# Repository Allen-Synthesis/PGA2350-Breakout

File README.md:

# PGA2350-breakout
### Pimoroni PGA2350 Breakout board for breadboard development of Eurorack modules

At the time I'm writing this, the only development board I can find for sale which utilises the B variant of the RP2350 *and* breaks out all of the extra ADCs it offers, is the [Pimoroni PGA2350](https://shop.pimoroni.com/products/pga2350?variant=42092629229651), however it is not a breadboard compatible.  
This board adapts the PGA2350 to allow it to be used for Eurorack development with a breadboard, breaking out all required connections including routing Eurorack power from a standard header to pin headers which can be connected to a breadboard's rails using jumper wire.  
The USB connections are arranged so that an [Adafruit USB Micro-B Breakout Board](https://www.adafruit.com/product/1833) (also sold by [Pimoroni](https://shop.pimoroni.com/products/adafruit-usb-micro-b-breakout-board?variant=821196557)) can be soldered directly to the board.

*NOTE: The first PCB order for these boards was tested on 10/09/2024 and appears to all work as expected. Not every GPIO has been tested, however the design is likely functional. Aesthetic improvements for version 1.1 (outlined below) have now been applied but no new boards have yet been ordered for testing. Order using the files in this repository with my blessing but at your own risk*

Pending changes based on version 1.0:
1. ~~Increment version to 1.1~~
1. ~~Alter pin header footprints to remove square pad for 1x2, 1x5, and 2x5~~
1. ~~Add JLC PCB order number text to the back~~
1. ~~Use consistent . or / in version date~~
1. ~~Remove J12 reference text~~
1. ~~Add ground stitching vias~~
1. ~~Use arrow to label PGA2350 and then use internal space to show orientation~~
1. Measure the USB breakout board and adjust position so that the edge is flush (USB already flush enough)
1. ~~Add lines between the labels and pins for rest of the headers as has been done for the GPIO headers~~
1. Add artwork to the back (and front?) to make use of the space (Text rearranged and logos swapped to copper layer, no more art added)

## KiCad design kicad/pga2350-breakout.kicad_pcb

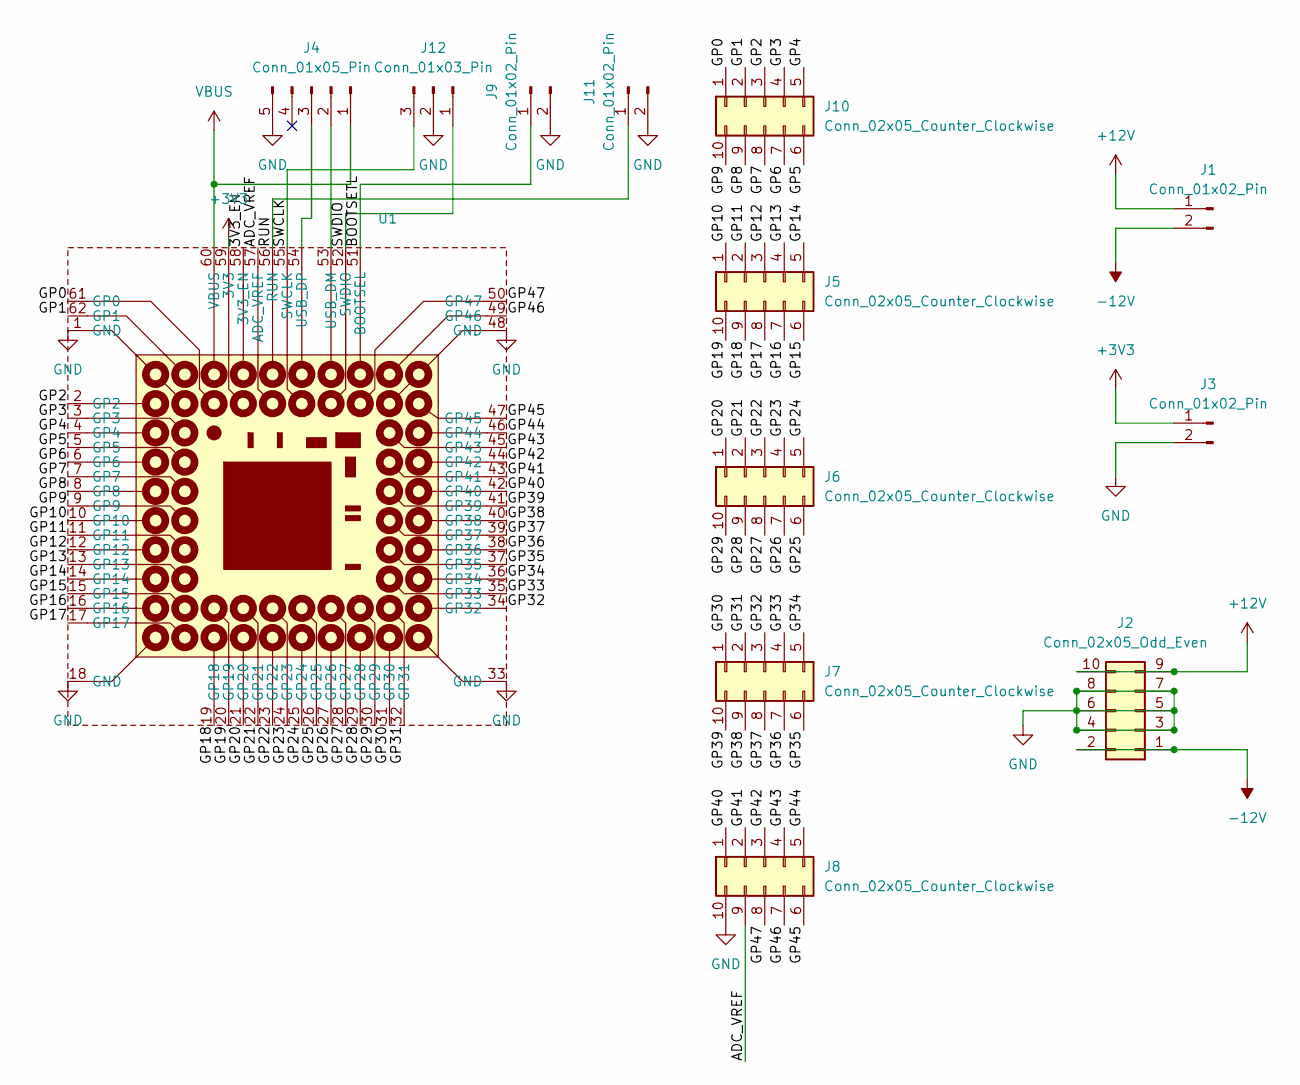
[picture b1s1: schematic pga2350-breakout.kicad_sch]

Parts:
J1, J3, J9, J11: Conn_01x02_Pin; pin-socket-2.54mm-01x02
J2: Conn_02x05_Odd_Even; power-header-10-pin
J4: Conn_01x05_Pin; pin-header-2.54mm-01x05
J5, J6, J7, J8, J10: Conn_02x05_Counter_Clockwise; pin-socket-2.54mm-02x05
J12: Conn_01x03_Pin; pin-header-2.54mm-01x03
U1: PGA2350

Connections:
+3V3: J3.1, U1.59 (3V3)
+12V: J1.1, J2.9, J2.10
-12V: J1.2, J2.1, J2.2
/3V3_EN: U1.58 (3V3_EN)
/ADC_VREF: J8.9, U1.57 (ADC_VREF)
/BOOTSETL: J9.1, U1.51 (BOOTSEL)
/GP0: J10.1, U1.61 (GP0)
/GP1: J10.2, U1.62 (GP1)
/GP2: J10.3, U1.2 (GP2)
/GP3: J10.4, U1.3 (GP3)
/GP4: J10.5, U1.4 (GP4)
/GP5: J10.6, U1.5 (GP5)
/GP6: J10.7, U1.6 (GP6)
/GP7: J10.8, U1.7 (GP7)
/GP8: J10.9, U1.8 (GP8)
/GP9: J10.10, U1.9 (GP9)
/GP10: J5.1, U1.10 (GP10)
/GP11: J5.2, U1.11 (GP11)
/GP12: J5.3, U1.12 (GP12)
/GP13: J5.4, U1.13 (GP13)
/GP14: J5.5, U1.14 (GP14)
/GP15: J5.6, U1.15 (GP15)
/GP16: J5.7, U1.16 (GP16)
/GP17: J5.8, U1.17 (GP17)
/GP18: J5.9, U1.19 (GP18)
/GP19: J5.10, U1.20 (GP19)
/GP20: J6.1, U1.21 (GP20)
/GP21: J6.2, U1.22 (GP21)
/GP22: J6.3, U1.23 (GP22)
/GP23: J6.4, U1.24 (GP23)
/GP24: J6.5, U1.25 (GP24)
/GP25: J6.6, U1.26 (GP25)
/GP26: J6.7, U1.27 (GP26)
/GP27: J6.8, U1.28 (GP27)
/GP28: J6.9, U1.29 (GP28)
/GP29: J6.10, U1.30 (GP29)
/GP30: J7.1, U1.31 (GP30)
/GP31: J7.2, U1.32 (GP31)
/GP32: J7.3, U1.34 (GP32)
/GP33: J7.4, U1.35 (GP33)
/GP34: J7.5, U1.36 (GP34)
/GP35: J7.6, U1.37 (GP35)
/GP36: J7.7, U1.38 (GP36)
/GP37: J7.8, U1.39 (GP37)
/GP38: J7.9, U1.40 (GP38)
/GP39: J7.10, U1.41 (GP39)
/GP40: J8.1, U1.42 (GP40)
/GP41: J8.2, U1.43 (GP41)
/GP42: J8.3, U1.44 (GP42)
/GP43: J8.4, U1.45 (GP43)
/GP44: J8.5, U1.46 (GP44)
/GP45: J8.6, U1.47 (GP45)
/GP46: J8.7, U1.49 (GP46)
/GP47: J8.8, U1.50 (GP47)
/RUN: J11.1, U1.56 (RUN)
/SWCLK: J12.3, U1.55 (SWCLK)
/SWDIO: J12.1, U1.52 (SWDIO)
GND: J2.3, J2.4, J2.5, J2.6, J2.7, J2.8, J3.2, J4.5, J8.10, J9.2, J11.2, J12.2, U1.1 (GND), U1.18 (GND), U1.33 (GND), U1.48 (GND)
unnamed: J4.2, U1.53 (USB_DM)
unnamed: J4.3, U1.54 (USB_DP)
VBUS: J4.1, U1.60 (VBUS)

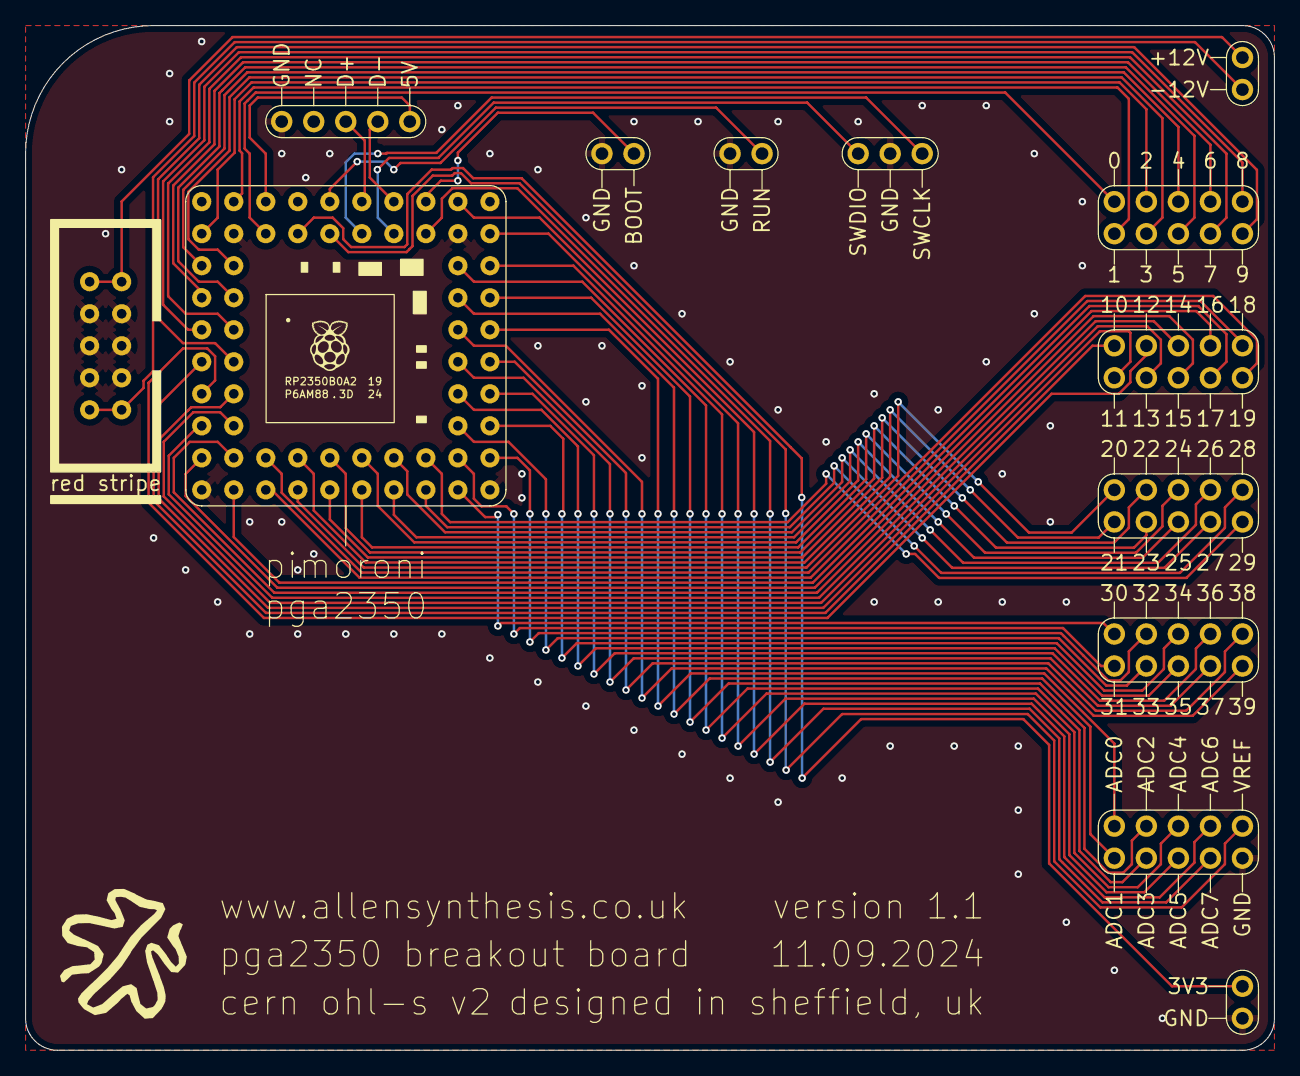
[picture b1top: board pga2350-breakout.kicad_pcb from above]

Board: 2 copper layers, 99.1 x 81.3 mm, 13 parts (0 on the bottom side), 60 nets.

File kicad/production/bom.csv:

Designator,Footprint,Quantity,Value,LCSC Part #
"J1, J11, J3, J9",pin-socket-2.54mm-01x02,4,Conn_01x02_Pin,
"J10, J5, J6, J7, J8",pin-socket-2.54mm-02x05,5,Conn_02x05_Counter_Clockwise,
J12,pin-header-2.54mm-01x03,1,Conn_01x03_Pin,
J2,power-header-10-pin,1,Conn_02x05_Odd_Even,
J4,pin-header-2.54mm-01x05,1,Conn_01x05_Pin,
U1,PGA2350,1,~,

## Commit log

2024-09-02 add kicad files
2024-09-02 initial routing, DRC all clear
2024-09-02 save
2024-09-02 save production version 1.0
2024-09-02 add image
2024-09-02 add image and usb note
2024-09-02 add adc note
2024-09-02 add brackets for clarity
2024-09-02 add high res ortho picture
2024-09-09 spelling
2024-09-09 add proposed changes for version 1.1
2024-09-09 add to proposed changes
2024-09-11 update note, add real photo
2024-09-11 reword tagline
2024-09-11 version 1.1 changes
2024-09-11 version 1.1 updates
2024-09-11 move pga2350 label
2024-09-11 add ground stitching vias
2024-09-11 stitchig vias added
2024-09-11 temp files
2024-09-11 various updates

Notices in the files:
kicad/pga2350-breakout.kicad_pcb:
cern ohl-s v2
